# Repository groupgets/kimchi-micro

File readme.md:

# kimχ micro

kimχ micro is a small and spicy open hardware embedded SBC that offers tons of
versitility for many different applications.

## Work in progress

This board is still a work in progress and is not yet considered production-
ready. If you wish to build this hardware yourself, expect that there may still
be some bugs.

## Features

### Application Processor

This project was undertaken with video encoding/decoding and wireless
connectivity in mind, so the i.MX8M Mini variant supports 1080p60 hardware video
encode/decode.

### Mini PCIe

The board can host a half- or full-mini PCIe module as often used for high-power
wifi chipsets. Mini PCIe is also perfect for other types of wireless such as LTE
and LoRa radios.

### USB-C

The board has a full-featured USB-C port with power source and sink
capabilities, as well as support for battery charging and power.

### Expansion

To enable different applications, kimχ micro has high-density expansion
connectors and a standard add-on module specification, as well as a Qwiic
connector for rapid prototyping or simple sensor integration.

## FAQ

### How do I pronounce kimχ

Like the spicy fermented cabbage (kimchi)

### Why did you call it that

So that when we make more of these boards, we can name them things like
saurkraut, sarmale, or cole slaw, and have a series of them called the cabbage
patch. But we really do love kimchi, and it has part of KiCad in it, and i.MX.

## License

The source files for this project are licensed under CERN-OHL-S V.2. This means
you are free to reuse all or part of this design in your own projects, provided
these projects also carry the same license.

Important Note
============
GroupGets does not provide coding, firmware, or software support of any kind and will not respond to related requests. All software and firmware provided by GroupGets are offered solely as examples or potential starting points. These repositories may be outdated and are not guaranteed to function as intended.

We do not accept returns or offer replacements due to issues related to software, firmware, or code compatibility.

The software is provided "AS IS", without warranty of any kind, express or implied, including but not limited to the warranties of merchantability, fitness for a particular purpose and non-infringement. In no event shall the authors or copyright holders be liable for any claim, damages, or other liability, whether in an action of contract, tort, or otherwise, arising from, out of, or in connection with the software or the use or other dealings in the software.

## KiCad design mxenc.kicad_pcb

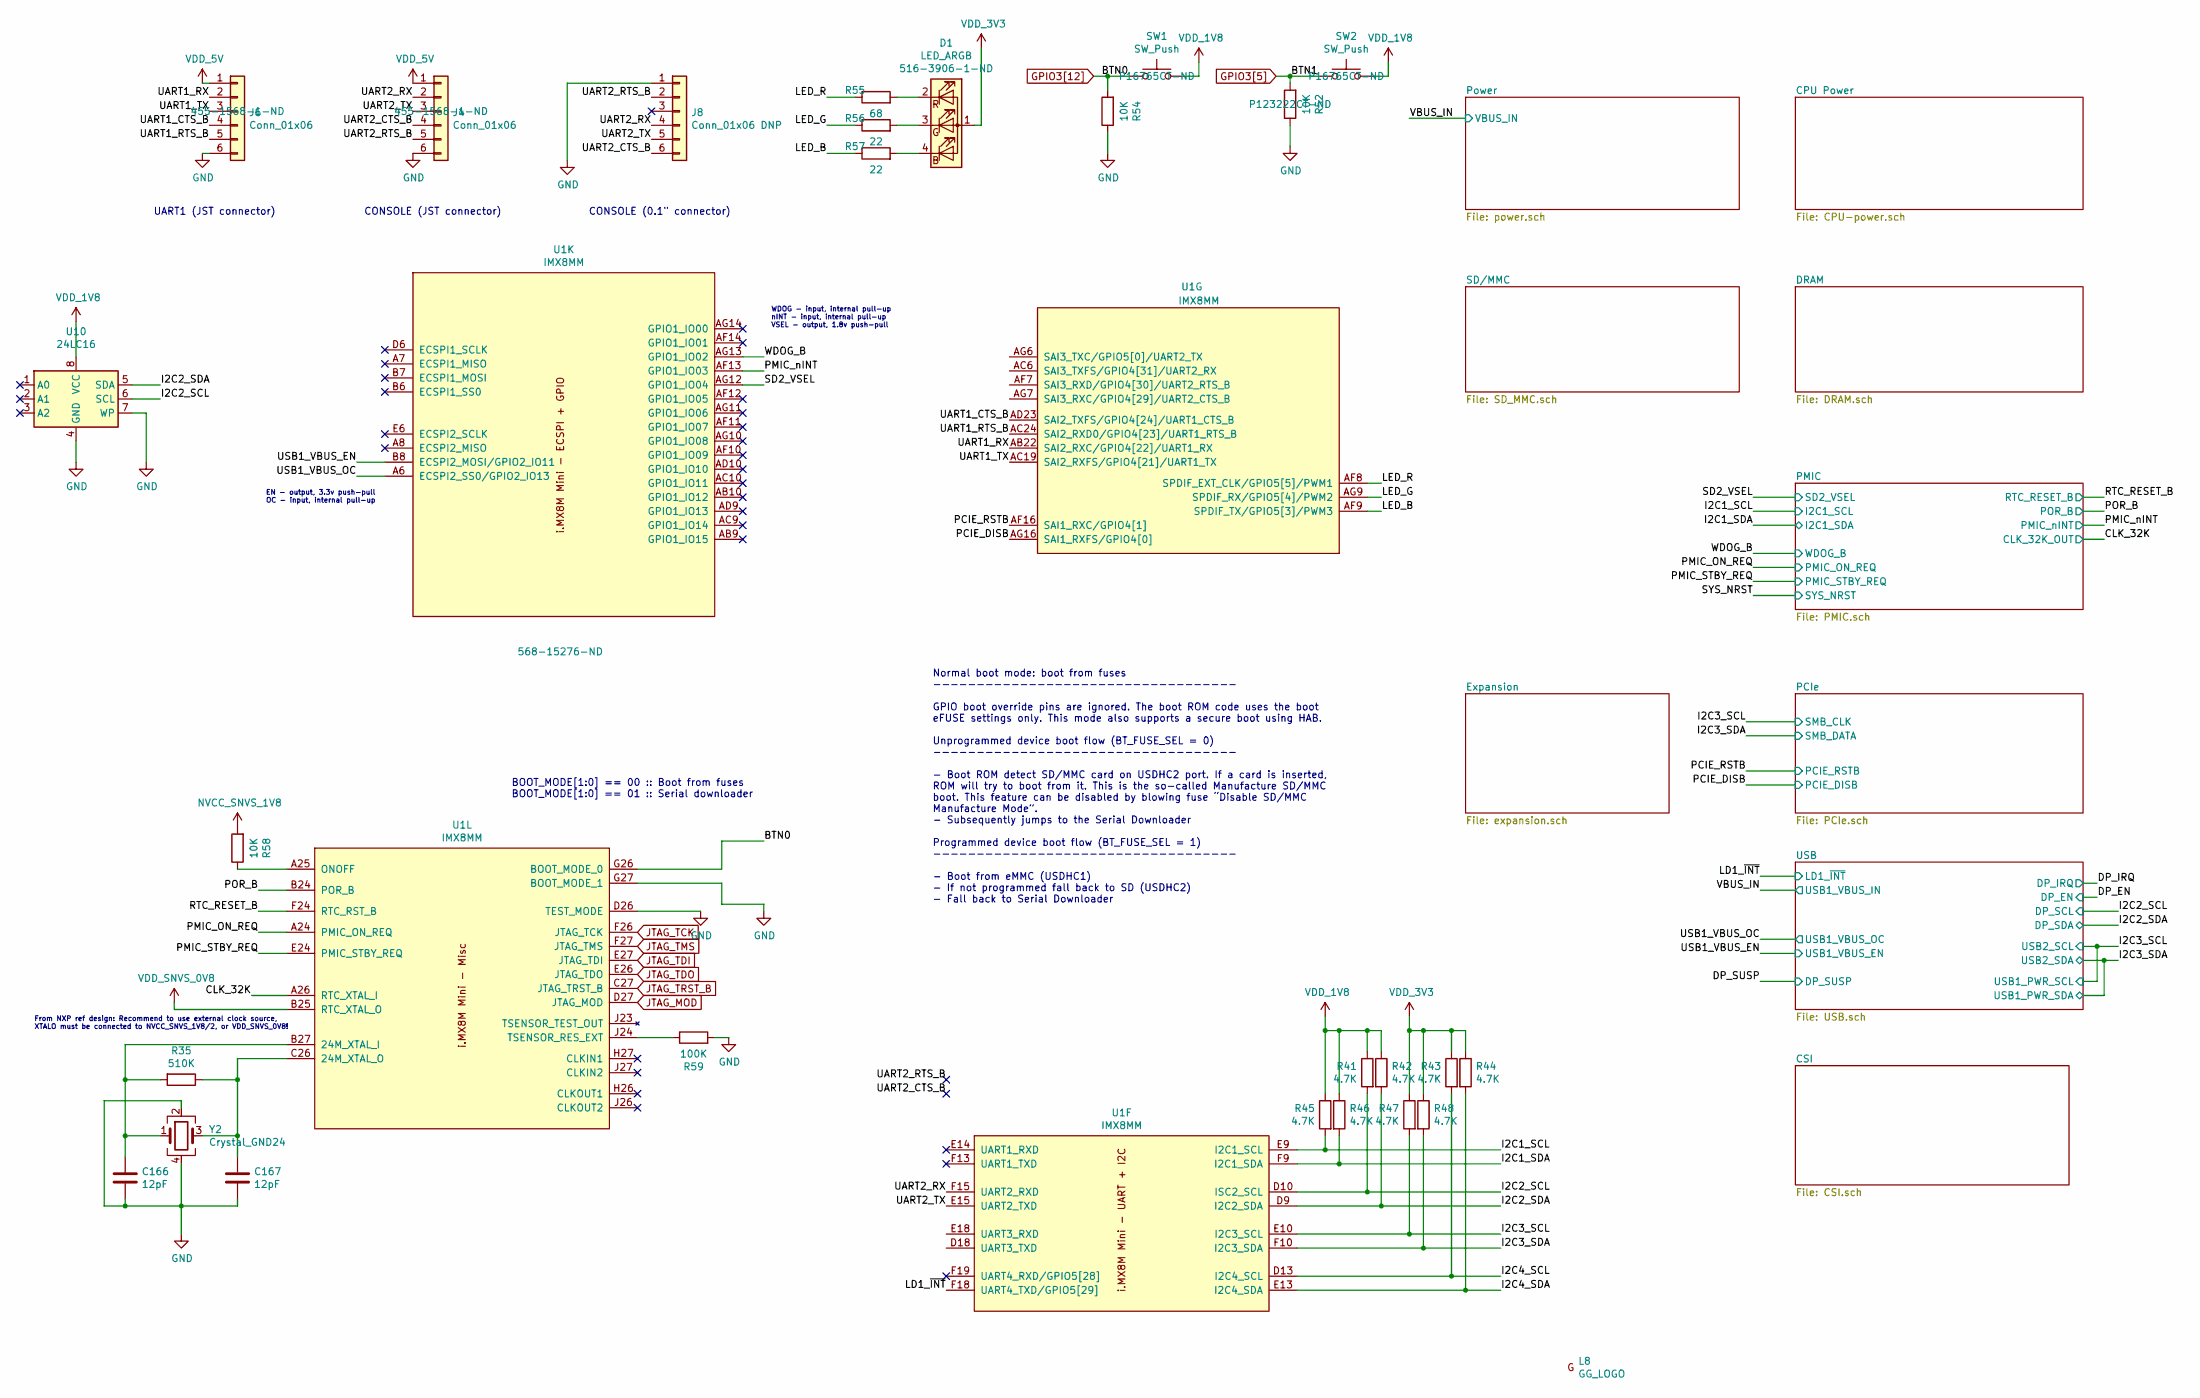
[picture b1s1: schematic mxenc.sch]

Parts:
C166, C167: 12pF; C_0201_0603Metric; Part CGA1A2C0G1E120J030BA
D1: LED_ARGB; LED_Cree-PLCC4_2x2mm_CW; Part ASMB-KTF0-0A306
J4, J6: Conn_01x06; JST_GH_SM06B-GHS-TB_1x06-1MP_P1.25mm_Horizontal; Part SM06B-GHS-TB(LF)(SN)
J8: Conn_01x06 DNP; PinHeader_1x06_P2.54mm_Horizontal
L8: GG_LOGO; gg-4x4
R35: 510K; R_0201_0603Metric; Part RC0201FR-07510KL
R41, R42, R43, R44, R45, R46, R47, R48: 4.7K; R_0201_0603Metric; Part RC0201JR-074K7L
R52, R54, R58: 10K; R_0201_0603Metric; Part ERJ-1GNJ103C
R55: 68; R_0201_0603Metric; Part RC0201JR-0768RL
R56, R57: 22; R_0201_0603Metric; Part RC0201JR-0722RL
R59: 100K; R_0201_0603Metric; Part RC0201JR-07100KL
SW1, SW2: SW_Push; SW_SPST_EVQP7C; Part EVQ-P7C01P
U1: IMX8MM; BGA-729_27x27_14.0x14.0mm; Part MIMX8MM6CVTKZAA
U10: 24LC16; DFN-8-1EP_3x2mm_P0.5mm_EP1.36x1.46mm; Part 24LC16B-I/MC
Y2: Crystal_GND24; XRCGB; Part XRCGB24M000F0L00R0

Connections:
/CLK_32K: U1.A26 (RTC_XTAL_I); also elsewhere on the board
/I2C1_SCL: R45.2, U1.E9 (I2C1_SCL); also elsewhere on the board
/I2C1_SDA: R46.2, U1.F9 (I2C1_SDA); also elsewhere on the board
/I2C2_SCL: R41.2, U1.D10 (ISC2_SCL), U10.6 (SCL)
/I2C2_SDA: R42.2, U1.D9 (I2C2_SDA), U10.5 (SDA)
/I2C3_SCL: R47.2, U1.E10 (I2C3_SCL); also elsewhere on the board
/I2C3_SDA: R48.2, U1.F10 (I2C3_SDA); also elsewhere on the board
/I2C4_SCL: R43.2, U1.D13 (I2C4_SCL)
/I2C4_SDA: R44.2, U1.E13 (I2C4_SDA)
/LD1_~INT: U1.F18 (UART4_TXD/GPIO5[29]); also elsewhere on the board
/LED_B: R57.1, U1.AF9 (SPDIF_TX/GPIO5[3]/PWM3)
/LED_G: R56.1, U1.AG9 (SPDIF_RX/GPIO5[4]/PWM2)
/LED_R: R55.1, U1.AF8 (SPDIF_EXT_CLK/GPIO5[5]/PWM1)
/PCIE_DISB: U1.AG16 (SAI1_RXFS/GPIO4[0]); also elsewhere on the board
/PCIE_RSTB: U1.AF16 (SAI1_RXC/GPIO4[1]); also elsewhere on the board
/PMIC_ON_REQ: U1.A24 (PMIC_ON_REQ); also elsewhere on the board
/PMIC_STBY_REQ: U1.E24 (PMIC_STBY_REQ); also elsewhere on the board
/PMIC_nINT: U1.AF13 (GPIO1_IO03); also elsewhere on the board
/POR_B: U1.B24 (POR_B); also elsewhere on the board
/RTC_RESET_B: U1.F24 (RTC_RST_B); also elsewhere on the board
/SD2_VSEL: U1.AG12 (GPIO1_IO04); also elsewhere on the board
/UART1_CTS_B: J6.4, U1.AD23 (SAI2_TXFS/GPIO4[24]/UART1_CTS_B)
/UART1_RTS_B: J6.5, U1.AC24 (SAI2_RXD0/GPIO4[23]/UART1_RTS_B)
/UART1_RX: J6.2, U1.AB22 (SAI2_RXC/GPIO4[22]/UART1_RX)
/UART1_TX: J6.3, U1.AC19 (SAI2_RXFS/GPIO4[21]/UART1_TX)
/UART2_CTS_B: J4.4, J8.6
/UART2_RTS_B: J4.5, J8.2
/UART2_RX: J4.2, J8.4, U1.F15 (UART2_RXD)
/UART2_TX: J4.3, J8.5, U1.E15 (UART2_TXD)
/WDOG_B: U1.AG13 (GPIO1_IO02); also elsewhere on the board
GND: C166.2, C167.2, J4.6, J6.6, J8.1, R52.1, R54.1, R59.2, U1.D26 (TEST_MODE), U1.G27 (BOOT_MODE_1), U10.4 (GND), U10.7 (WP), Y2.2, Y2.4; also elsewhere on the board
GPIO3[5]: R52.2, SW2.1; also elsewhere on the board
GPIO3[12]: R54.2, SW1.1, U1.G26 (BOOT_MODE_0); also elsewhere on the board
JTAG_MOD: U1.D27 (JTAG_MOD); also elsewhere on the board
JTAG_TCK: U1.F26 (JTAG_TCK); also elsewhere on the board
JTAG_TDI: U1.E27 (JTAG_TDI); also elsewhere on the board
JTAG_TDO: U1.E26 (JTAG_TDO); also elsewhere on the board
JTAG_TMS: U1.F27 (JTAG_TMS); also elsewhere on the board
JTAG_TRST_B: U1.C27 (JTAG_TRST_B); also elsewhere on the board
NVCC_1V8: R41.1, R42.1, R45.1, R46.1, SW1.2, SW2.2, U10.8 (VCC); also elsewhere on the board
NVCC_3V3: D1.1 (A), R43.1, R44.1, R47.1, R48.1; also elsewhere on the board
NVCC_SNVS_1V8: R58.2; also elsewhere on the board
unnamed: C166.1, R35.2, U1.B27 (24M_XTAL_I), Y2.1
unnamed: C167.1, R35.1, U1.C26 (24M_XTAL_O), Y2.3
unnamed: D1.2 (RK), R55.2
unnamed: D1.3 (GK), R56.2
unnamed: D1.4 (BK), R57.2
unnamed: R58.1, U1.A25 (ONOFF)
unnamed: R59.1, U1.J24 (TSENSOR_RES_EXT)
VDD_5V: J4.1, J6.1; also elsewhere on the board
VDD_SNVS_0V8: U1.B25 (RTC_XTAL_O); also elsewhere on the board

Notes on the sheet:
CONSOLE (JST connector)
UART1 (JST connector)
CONSOLE (0.1" connector)
From NXP ref design: Recommend to use external clock source, XTALO must be connected to NVCC_SNVS_1V8/2, or VDD_SNVS_0V8!
BOOT_MODE[1:0] == 00 :: Boot from fuses BOOT_MODE[1:0] == 01 :: Serial downloader
Normal boot mode: boot from fuses ----------------------------------- GPIO boot override pins are ignored. The boot ROM code uses the boot eFUSE settings only. This mode also supports a secure boot using HAB. Unprogrammed device boot flow (BT_FUSE_SEL = 0) ----------------------------------- - Boot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
EN - output, 3.3v push-pull OC - input, internal pull-up
WDOG - input, internal pull-up nINT - input, internal pull-up VSEL - output, 1.8v push-pull

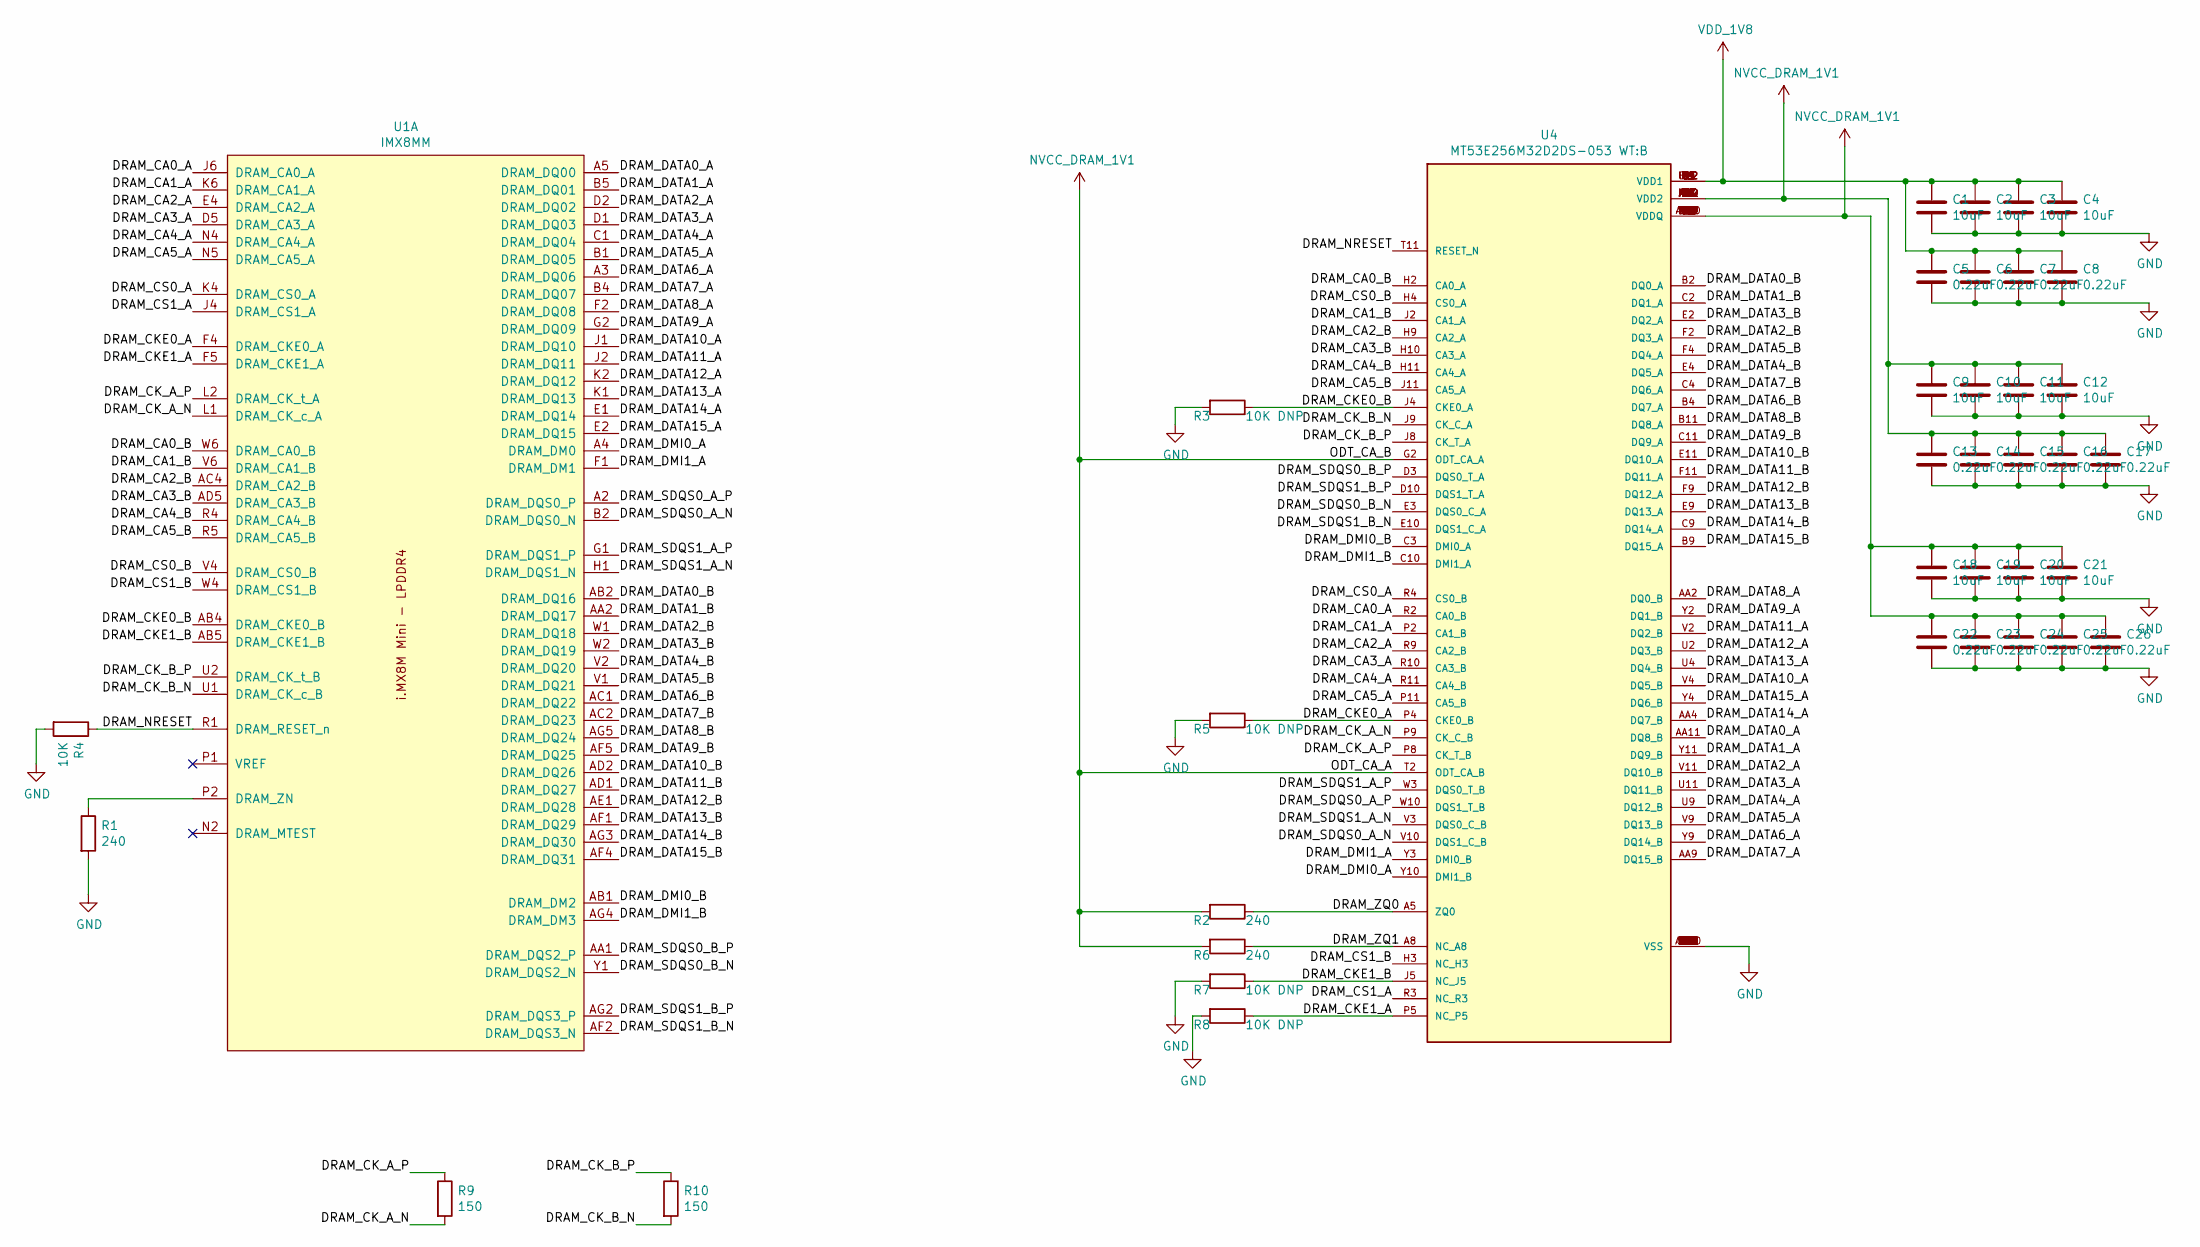
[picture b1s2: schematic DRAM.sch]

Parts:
C1, C2, C3, C4, C9, C10, C11, C12, C18, C19, C20, C21: 10uF; C_0402_1005Metric; Part GRM155C80J106ME11D
C5, C6, C7, C8, C13, C14, C15, C16, C17, C22, C23, C24, C25, C26: 0.22uF; C_0402_1005Metric; Part GRM155C8YA224ME01D
R1, R2, R6: 240; R_0402_1005Metric; Part RC0402FR-07240RP
R3, R5, R7, R8: 10K DNP; R_0402_1005Metric
R4: 10K; R_0402_1005Metric; Part ERJ-2GEJ103X
R9, R10: 150; R_0402_1005Metric; Part RC0402FR-07150RL
U1: IMX8MM; BGA-729_27x27_14.0x14.0mm; Part MIMX8MM6CVTKZAA
U4: MT53E256M32D2DS-053 WT:B; BGA200C80X65P12X22_1100X1450X80N; Part MT53E256M32D2DS-053 WT:B

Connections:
/DRAM/DRAM_CA0_A: U1.J6 (DRAM_CA0_A), U4.R2 (CA0_B)
/DRAM/DRAM_CA0_B: U1.W6 (DRAM_CA0_B), U4.H2 (CA0_A)
/DRAM/DRAM_CA1_A: U1.K6 (DRAM_CA1_A), U4.P2 (CA1_B)
/DRAM/DRAM_CA1_B: U1.V6 (DRAM_CA1_B), U4.J2 (CA1_A)
/DRAM/DRAM_CA2_A: U1.E4 (DRAM_CA2_A), U4.R9 (CA2_B)
/DRAM/DRAM_CA2_B: U1.AC4 (DRAM_CA2_B), U4.H9 (CA2_A)
/DRAM/DRAM_CA3_A: U1.D5 (DRAM_CA3_A), U4.R10 (CA3_B)
/DRAM/DRAM_CA3_B: U1.AD5 (DRAM_CA3_B), U4.H10 (CA3_A)
/DRAM/DRAM_CA4_A: U1.N4 (DRAM_CA4_A), U4.R11 (CA4_B)
/DRAM/DRAM_CA4_B: U1.R4 (DRAM_CA4_B), U4.H11 (CA4_A)
/DRAM/DRAM_CA5_A: U1.N5 (DRAM_CA5_A), U4.P11 (CA5_B)
/DRAM/DRAM_CA5_B: U1.R5 (DRAM_CA5_B), U4.J11 (CA5_A)
/DRAM/DRAM_CKE0_A: R5.1, U1.F4 (DRAM_CKE0_A), U4.P4 (CKE0_B)
/DRAM/DRAM_CKE0_B: R3.1, U1.AB4 (DRAM_CKE0_B), U4.J4 (CKE0_A)
/DRAM/DRAM_CKE1_A: R8.1, U1.F5 (DRAM_CKE1_A), U4.P5 (NC_P5)
/DRAM/DRAM_CKE1_B: R7.1, U1.AB5 (DRAM_CKE1_B), U4.J5 (NC_J5)
/DRAM/DRAM_CK_A_N: R9.2, U1.L1 (DRAM_CK_c_A), U4.P9 (CK_C_B)
/DRAM/DRAM_CK_A_P: R9.1, U1.L2 (DRAM_CK_t_A), U4.P8 (CK_T_B)
/DRAM/DRAM_CK_B_N: R10.2, U1.U1 (DRAM_CK_c_B), U4.J9 (CK_C_A)
/DRAM/DRAM_CK_B_P: R10.1, U1.U2 (DRAM_CK_t_B), U4.J8 (CK_T_A)
/DRAM/DRAM_CS0_A: U1.K4 (DRAM_CS0_A), U4.R4 (CS0_B)
/DRAM/DRAM_CS0_B: U1.V4 (DRAM_CS0_B), U4.H4 (CS0_A)
/DRAM/DRAM_CS1_A: U1.J4 (DRAM_CS1_A), U4.R3 (NC_R3)
/DRAM/DRAM_CS1_B: U1.W4 (DRAM_CS1_B), U4.H3 (NC_H3)
/DRAM/DRAM_DATA0_A: U1.A5 (DRAM_DQ00), U4.AA11 (DQ8_B)
/DRAM/DRAM_DATA0_B: U1.AB2 (DRAM_DQ16), U4.B2 (DQ0_A)
/DRAM/DRAM_DATA1_A: U1.B5 (DRAM_DQ01), U4.Y11 (DQ9_B)
/DRAM/DRAM_DATA1_B: U1.AA2 (DRAM_DQ17), U4.C2 (DQ1_A)
/DRAM/DRAM_DATA2_A: U1.D2 (DRAM_DQ02), U4.V11 (DQ10_B)
/DRAM/DRAM_DATA2_B: U1.W1 (DRAM_DQ18), U4.F2 (DQ3_A)
/DRAM/DRAM_DATA3_A: U1.D1 (DRAM_DQ03), U4.U11 (DQ11_B)
/DRAM/DRAM_DATA3_B: U1.W2 (DRAM_DQ19), U4.E2 (DQ2_A)
/DRAM/DRAM_DATA4_A: U1.C1 (DRAM_DQ04), U4.U9 (DQ12_B)
/DRAM/DRAM_DATA4_B: U1.V2 (DRAM_DQ20), U4.E4 (DQ5_A)
/DRAM/DRAM_DATA5_A: U1.B1 (DRAM_DQ05), U4.V9 (DQ13_B)
/DRAM/DRAM_DATA5_B: U1.V1 (DRAM_DQ21), U4.F4 (DQ4_A)
/DRAM/DRAM_DATA6_A: U1.A3 (DRAM_DQ06), U4.Y9 (DQ14_B)
/DRAM/DRAM_DATA6_B: U1.AC1 (DRAM_DQ22), U4.B4 (DQ7_A)
/DRAM/DRAM_DATA7_A: U1.B4 (DRAM_DQ07), U4.AA9 (DQ15_B)
/DRAM/DRAM_DATA7_B: U1.AC2 (DRAM_DQ23), U4.C4 (DQ6_A)
/DRAM/DRAM_DATA8_A: U1.F2 (DRAM_DQ08), U4.AA2 (DQ0_B)
/DRAM/DRAM_DATA8_B: U1.AG5 (DRAM_DQ24), U4.B11 (DQ8_A)
/DRAM/DRAM_DATA9_A: U1.G2 (DRAM_DQ09), U4.Y2 (DQ1_B)
/DRAM/DRAM_DATA9_B: U1.AF5 (DRAM_DQ25), U4.C11 (DQ9_A)
/DRAM/DRAM_DATA10_A: U1.J1 (DRAM_DQ10), U4.V4 (DQ5_B)
/DRAM/DRAM_DATA10_B: U1.AD2 (DRAM_DQ26), U4.E11 (DQ10_A)
/DRAM/DRAM_DATA11_A: U1.J2 (DRAM_DQ11), U4.V2 (DQ2_B)
/DRAM/DRAM_DATA11_B: U1.AD1 (DRAM_DQ27), U4.F11 (DQ11_A)
/DRAM/DRAM_DATA12_A: U1.K2 (DRAM_DQ12), U4.U2 (DQ3_B)
/DRAM/DRAM_DATA12_B: U1.AE1 (DRAM_DQ28), U4.F9 (DQ12_A)
/DRAM/DRAM_DATA13_A: U1.K1 (DRAM_DQ13), U4.U4 (DQ4_B)
/DRAM/DRAM_DATA13_B: U1.AF1 (DRAM_DQ29), U4.E9 (DQ13_A)
/DRAM/DRAM_DATA14_A: U1.E1 (DRAM_DQ14), U4.AA4 (DQ7_B)
/DRAM/DRAM_DATA14_B: U1.AG3 (DRAM_DQ30), U4.C9 (DQ14_A)
/DRAM/DRAM_DATA15_A: U1.E2 (DRAM_DQ15), U4.Y4 (DQ6_B)
/DRAM/DRAM_DATA15_B: U1.AF4 (DRAM_DQ31), U4.B9 (DQ15_A)
/DRAM/DRAM_DMI0_A: U1.A4 (DRAM_DM0), U4.Y10 (DMI1_B)
/DRAM/DRAM_DMI0_B: U1.AB1 (DRAM_DM2), U4.C3 (DMI0_A)
/DRAM/DRAM_DMI1_A: U1.F1 (DRAM_DM1), U4.Y3 (DMI0_B)
/DRAM/DRAM_DMI1_B: U1.AG4 (DRAM_DM3), U4.C10 (DMI1_A)
/DRAM/DRAM_NRESET: R4.1, U1.R1 (DRAM_RESET_n), U4.T11 (RESET_N)
/DRAM/DRAM_SDQS0_A_N: U1.B2 (DRAM_DQS0_N), U4.V10 (DQS1_C_B)
/DRAM/DRAM_SDQS0_A_P: U1.A2 (DRAM_DQS0_P), U4.W10 (DQS1_T_B)
/DRAM/DRAM_SDQS0_B_N: U1.Y1 (DRAM_DQS2_N), U4.E3 (DQS0_C_A)
/DRAM/DRAM_SDQS0_B_P: U1.AA1 (DRAM_DQS2_P), U4.D3 (DQS0_T_A)
/DRAM/DRAM_SDQS1_A_N: U1.H1 (DRAM_DQS1_N), U4.V3 (DQS0_C_B)
/DRAM/DRAM_SDQS1_A_P: U1.G1 (DRAM_DQS1_P), U4.W3 (DQS0_T_B)
/DRAM/DRAM_SDQS1_B_N: U1.AF2 (DRAM_DQS3_N), U4.E10 (DQS1_C_A)
/DRAM/DRAM_SDQS1_B_P: U1.AG2 (DRAM_DQS3_P), U4.D10 (DQS1_T_A)
/DRAM/DRAM_ZQ0: R2.1, U4.A5 (ZQ0)
/DRAM/DRAM_ZQ1: R6.1, U4.A8 (NC_A8)
GND: C1.2, C2.2, C3.2, C4.2, C5.2, C6.2, C7.2, C8.2, C9.2, C10.2, C11.2, C12.2, C13.2, C14.2, C15.2, C16.2, C17.2, C18.2, C19.2, C20.2, C21.2, C22.2, C23.2, C24.2, C25.2, C26.2, R1.2, R3.2, R4.2, R5.2, R7.2, R8.2, U4.A3 (VSS), U4.A10 (VSS), U4.AB3 (VSS), U4.AB5 (VSS), U4.AB8 (VSS), U4.AB10 (VSS), U4.C1 (VSS), U4.C5 (VSS), U4.C8 (VSS), U4.C12 (VSS), U4.D2 (VSS), U4.D4 (VSS), U4.D9 (VSS), U4.D11 (VSS), U4.E1 (VSS), U4.E5 (VSS), U4.E8 (VSS), U4.E12 (VSS), U4.G1 (VSS), U4.G3 (VSS), U4.G5 (VSS), U4.G8 (VSS), U4.G10 (VSS), U4.G12 (VSS), U4.J1 (VSS), U4.J3 (VSS), U4.J10 (VSS), U4.J12 (VSS), U4.K2 (VSS), U4.K4 (VSS), U4.K9 (VSS), U4.K11 (VSS), U4.N2 (VSS), U4.N4 (VSS), U4.N9 (VSS), U4.N11 (VSS), U4.P1 (VSS), U4.P3 (VSS), U4.P10 (VSS), U4.P12 (VSS), U4.T1 (VSS), U4.T3 (VSS), U4.T5 (VSS), U4.T8 (VSS), U4.T10 (VSS), U4.T12 (VSS), U4.V1 (VSS), U4.V5 (VSS), U4.V8 (VSS), U4.V12 (VSS), U4.W2 (VSS), U4.W4 (VSS), U4.W9 (VSS), U4.W11 (VSS), U4.Y1 (VSS), U4.Y5 (VSS), U4.Y8 (VSS), U4.Y12 (VSS); also elsewhere on the board
NVCC_1V8: C1.1, C2.1, C3.1, C4.1, C5.1, C6.1, C7.1, C8.1, U4.F1 (VDD1), U4.F12 (VDD1), U4.G4 (VDD1), U4.G9 (VDD1), U4.T4 (VDD1), U4.T9 (VDD1), U4.U1 (VDD1), U4.U12 (VDD1); also elsewhere on the board
NVCC_DRAM_1V1: C9.1, C10.1, C11.1, C12.1, C13.1, C14.1, C15.1, C16.1, C17.1, C18.1, C19.1, C20.1, C21.1, C22.1, C23.1, C24.1, C25.1, C26.1, R2.2, R6.2, U4.A4 (VDD2), U4.A9 (VDD2), U4.AA3 (VDDQ), U4.AA5 (VDDQ), U4.AA8 (VDDQ), U4.AA10 (VDDQ), U4.AB4 (VDD2), U4.AB9 (VDD2), U4.B3 (VDDQ), U4.B5 (VDDQ), U4.B8 (VDDQ), U4.B10 (VDDQ), U4.D1 (VDDQ), U4.D5 (VDDQ), U4.D8 (VDDQ), U4.D12 (VDDQ), U4.F3 (VDDQ), U4.F5 (VDD2), U4.F8 (VDD2), U4.F10 (VDDQ), U4.G2 (ODT_CA_A), U4.H1 (VDD2), U4.H5 (VDD2), U4.H8 (VDD2), U4.H12 (VDD2), U4.K1 (VDD2), U4.K3 (VDD2), U4.K10 (VDD2), U4.K12 (VDD2), U4.N1 (VDD2), U4.N3 (VDD2), U4.N10 (VDD2), U4.N12 (VDD2), U4.R1 (VDD2), U4.R5 (VDD2), U4.R8 (VDD2), U4.R12 (VDD2), U4.T2 (ODT_CA_B), U4.U3 (VDDQ), U4.U5 (VDD2), U4.U8 (VDD2), U4.U10 (VDDQ), U4.W1 (VDDQ), U4.W5 (VDDQ), U4.W8 (VDDQ), U4.W12 (VDDQ); also elsewhere on the board
unnamed: R1.1, U1.P2 (DRAM_ZN)

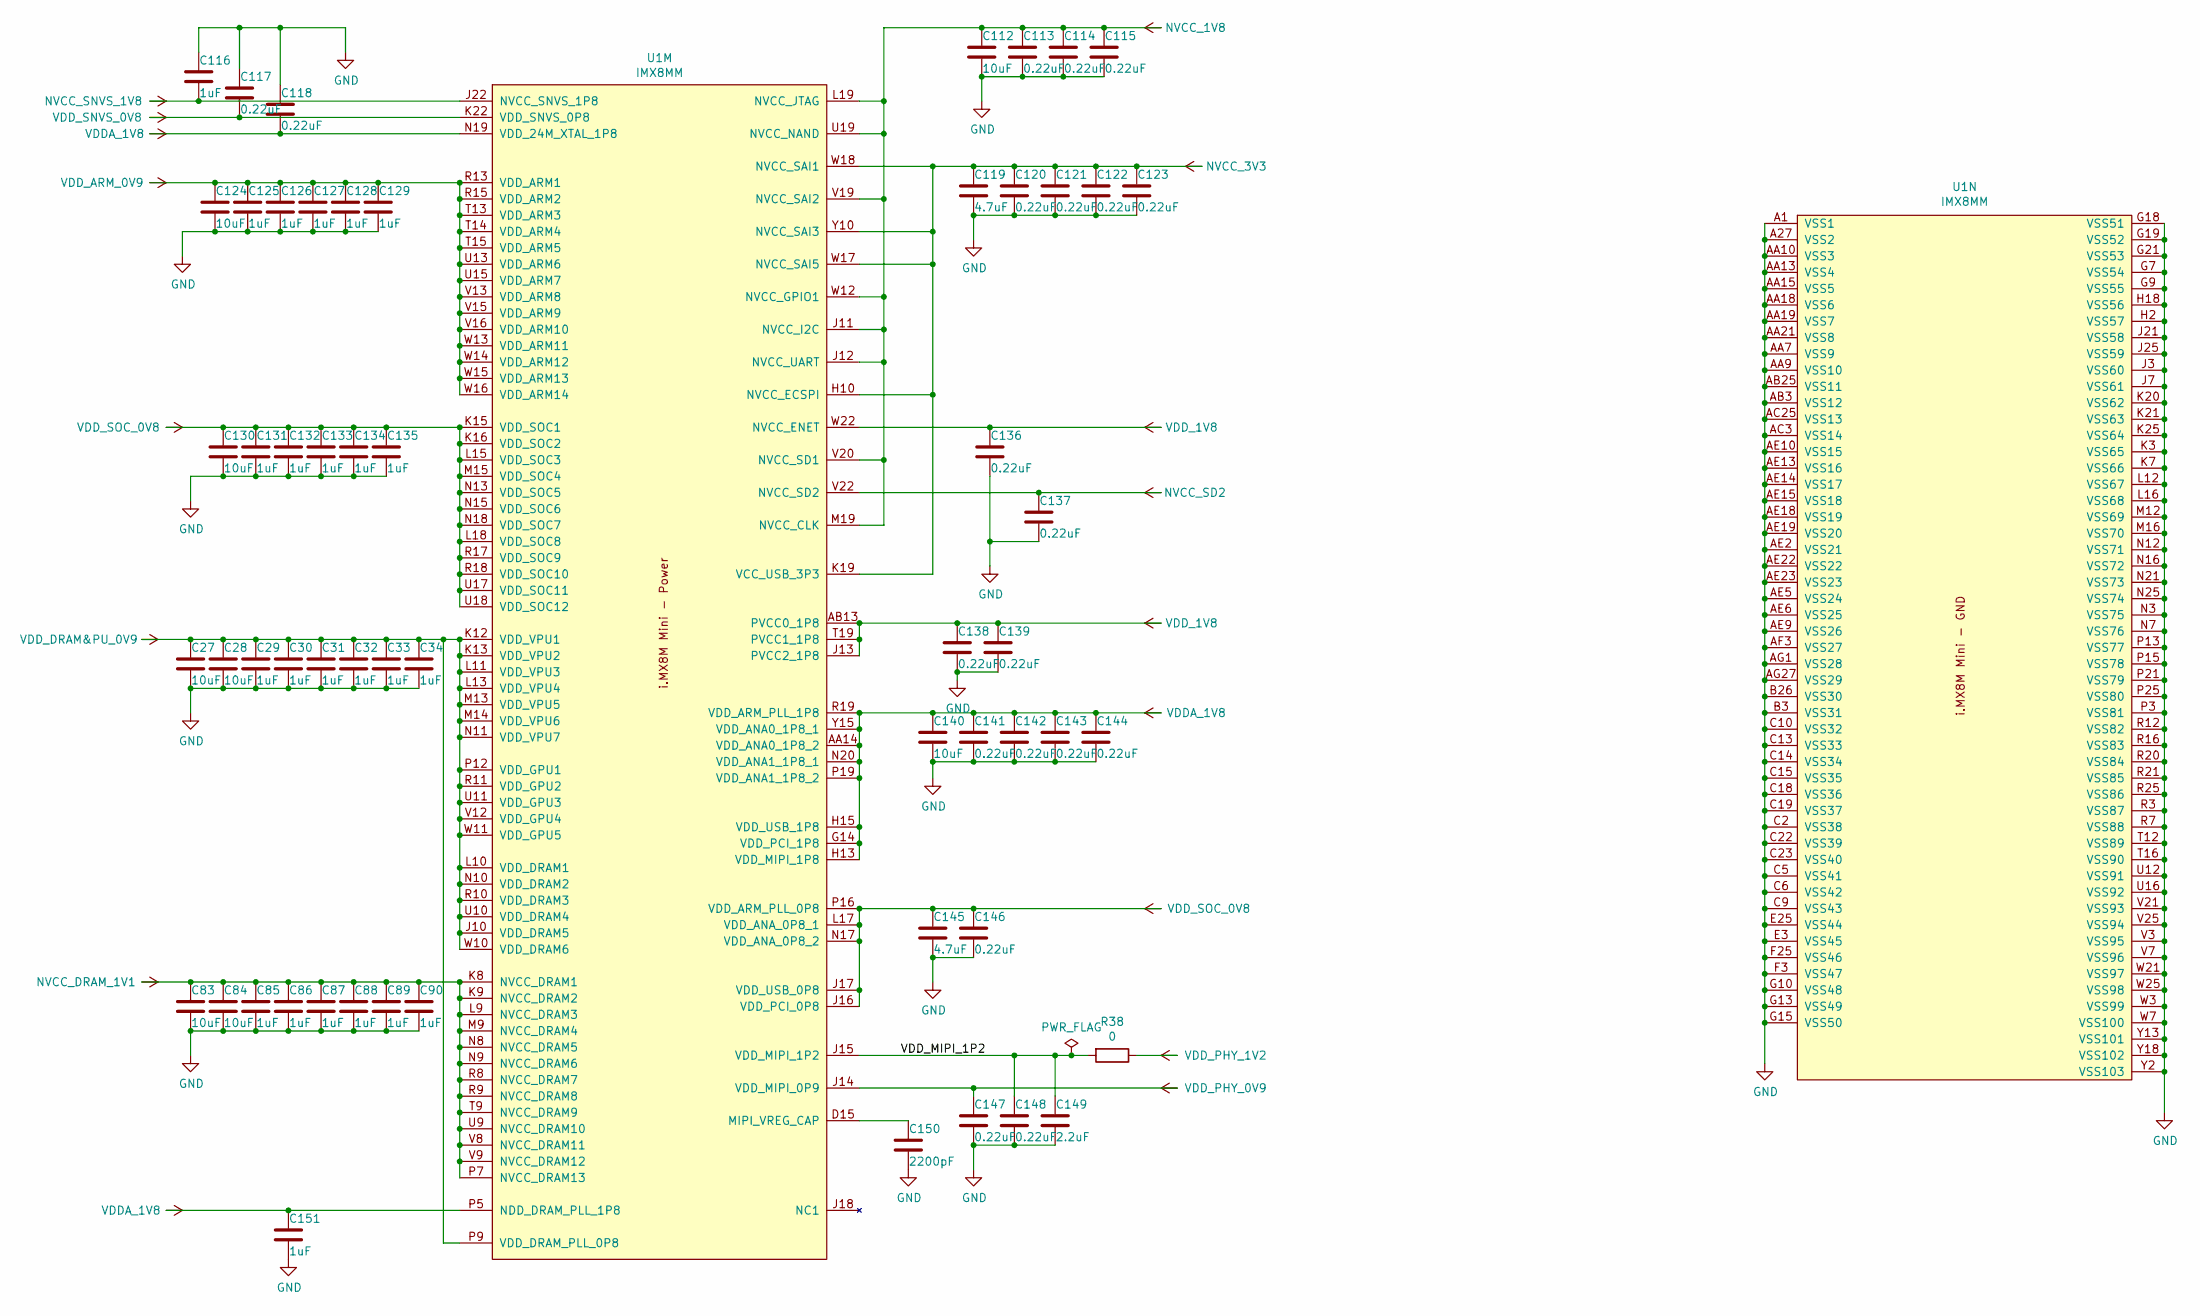
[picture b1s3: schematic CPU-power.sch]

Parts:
C27, C28, C83, C84, C112, C124, C130, C140: 10uF; C_0402_1005Metric; Part GRM155C80J106ME11D
C29, C30, C31, C32, C33, C34, C85, C86, C87, C88, C89, C90, C116, C125, C126, C127, C128, C129, C131, C132, C133, C134, C135, C151: 1uF; C_0201_0603Metric; Part GRM033C80G105ME05D
C113, C114, C115, C117, C118, C120, C121, C122, C123, C136, C137, C138, C139, C141, C142, C143, C144, C146, C147, C148: 0.22uF; C_0201_0603Metric; Part GRM033C80J224KE90D
C119, C145: 4.7uF; C_0402_1005Metric; Part GRM155C80J475MEAAD
C149: 2.2uF; C_0201_0603Metric; Part GRM033D80E225ME47D
C150: 2200pF; C_0201_0603Metric; Part GRM033R70J222KA01D
R38: 0; R_0402_1005Metric; Part RC0402JR-070RL
U1: IMX8MM; BGA-729_27x27_14.0x14.0mm; Part MIMX8MM6CVTKZAA

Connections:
/CPU Power/VDD_MIPI_1P2: C148.1, C149.1, R38.2, U1.J15 (VDD_MIPI_1P2)
GND: C27.2, C28.2, C29.2, C30.2, C31.2, C32.2, C33.2, C34.2, C83.2, C84.2, C85.2, C86.2, C87.2, C88.2, C89.2, C90.2, C112.2, C113.2, C114.2, C115.2, C116.1, C117.1, C118.1, C119.2, C120.2, C121.2, C122.2, C123.2, C124.2, C125.2, C126.2, C127.2, C128.2, C129.2, C130.2, C131.2, C132.2, C133.2, C134.2, C135.2, C136.2, C137.2, C138.2, C139.2, C140.2, C141.2, C142.2, C143.2, C144.2, C145.2, C146.2, C147.2, C148.2, C149.2, C150.2, C151.2, U1.A1 (VSS1), U1.A27 (VSS2), U1.AA7 (VSS9), U1.AA9 (VSS10), U1.AA10 (VSS3), U1.AA13 (VSS4), U1.AA15 (VSS5), U1.AA18 (VSS6), U1.AA19 (VSS7), U1.AA21 (VSS8), U1.AB3 (VSS12), U1.AB25 (VSS11), U1.AC3 (VSS14), U1.AC25 (VSS13), U1.AE2 (VSS21), U1.AE5 (VSS24), U1.AE6 (VSS25), U1.AE9 (VSS26), U1.AE10 (VSS15), U1.AE13 (VSS16), U1.AE14 (VSS17), U1.AE15 (VSS18), U1.AE18 (VSS19), U1.AE19 (VSS20), U1.AE22 (VSS22), U1.AE23 (VSS23), U1.AF3 (VSS27), U1.AG1 (VSS28), U1.AG27 (VSS29), U1.B3 (VSS31), U1.B26 (VSS30), U1.C2 (VSS38), U1.C5 (VSS41), U1.C6 (VSS42), U1.C9 (VSS43), U1.C10 (VSS32), U1.C13 (VSS33), U1.C14 (VSS34), U1.C15 (VSS35), U1.C18 (VSS36), U1.C19 (VSS37), U1.C22 (VSS39), U1.C23 (VSS40), U1.E3 (VSS45), U1.E25 (VSS44), U1.F3 (VSS47), U1.F25 (VSS46), U1.G7 (VSS54), U1.G9 (VSS55), U1.G10 (VSS48), U1.G13 (VSS49), U1.G15 (VSS50), U1.G18 (VSS51), U1.G19 (VSS52), U1.G21 (VSS53), U1.H2 (VSS57), U1.H18 (VSS56), U1.J3 (VSS60), U1.J7 (VSS61), U1.J21 (VSS58), U1.J25 (VSS59), U1.K3 (VSS65), U1.K7 (VSS66), U1.K20 (VSS62), U1.K21 (VSS63), U1.K25 (VSS64), U1.L12 (VSS67), U1.L16 (VSS68), U1.M12 (VSS69), U1.M16 (VSS70), U1.N3 (VSS75), U1.N7 (VSS76), U1.N12 (VSS71), U1.N16 (VSS72), U1.N21 (VSS73), U1.N25 (VSS74), U1.P3 (VSS81), U1.P13 (VSS77), U1.P15 (VSS78), U1.P21 (VSS79), U1.P25 (VSS80), U1.R3 (VSS87), U1.R7 (VSS88), U1.R12 (VSS82), U1.R16 (VSS83), U1.R20 (VSS84), U1.R21 (VSS85), U1.R25 (VSS86), U1.T12 (VSS89), U1.T16 (VSS90), U1.U12 (VSS91), U1.U16 (VSS92), U1.V3 (VSS95), U1.V7 (VSS96), U1.V21 (VSS93), U1.V25 (VSS94), U1.W3 (VSS99), U1.W7 (VSS100), U1.W21 (VSS97), U1.W25 (VSS98), U1.Y2 (VSS103), U1.Y13 (VSS101), U1.Y18 (VSS102); also elsewhere on the board
NVCC_1V8: C112.1, C113.1, C114.1, C115.1, C136.1, C138.1, C139.1, U1.AB13 (PVCC0_1P8), U1.J11 (NVCC_I2C), U1.J12 (NVCC_UART), U1.J13 (PVCC2_1P8), U1.L19 (NVCC_JTAG), U1.M19 (NVCC_CLK), U1.T19 (PVCC1_1P8), U1.U19 (NVCC_NAND), U1.V19 (NVCC_SAI2), U1.V20 (NVCC_SD1), U1.W12 (NVCC_GPIO1), U1.W22 (NVCC_ENET); also elsewhere on the board
NVCC_3V3: C119.1, C120.1, C121.1, C122.1, C123.1, U1.H10 (NVCC_ECSPI), U1.K19 (VCC_USB_3P3), U1.W17 (NVCC_SAI5), U1.W18 (NVCC_SAI1), U1.Y10 (NVCC_SAI3); also elsewhere on the board
NVCC_DRAM_1V1: C83.1, C84.1, C85.1, C86.1, C87.1, C88.1, C89.1, C90.1, U1.K8 (NVCC_DRAM1), U1.K9 (NVCC_DRAM2), U1.L9 (NVCC_DRAM3), U1.M9 (NVCC_DRAM4), U1.N8 (NVCC_DRAM5), U1.N9 (NVCC_DRAM6), U1.P7 (NVCC_DRAM13), U1.R8 (NVCC_DRAM7), U1.R9 (NVCC_DRAM8), U1.T9 (NVCC_DRAM9), U1.U9 (NVCC_DRAM10), U1.V8 (NVCC_DRAM11), U1.V9 (NVCC_DRAM12); also elsewhere on the board
NVCC_SD2: C137.1, U1.V22 (NVCC_SD2); also elsewhere on the board
NVCC_SNVS_1V8: C116.2, U1.J22 (NVCC_SNVS_1P8); also elsewhere on the board
unnamed: C150.1, U1.D15 (MIPI_VREG_CAP)
VDDA_1V8: C118.2, C140.1, C141.1, C142.1, C143.1, C144.1, C151.1, U1.AA14 (VDD_ANA0_1P8_2), U1.G14 (VDD_PCI_1P8), U1.H13 (VDD_MIPI_1P8), U1.H15 (VDD_USB_1P8), U1.N19 (VDD_24M_XTAL_1P8), U1.N20 (VDD_ANA1_1P8_1), U1.P5 (NDD_DRAM_PLL_1P8), U1.P19 (VDD_ANA1_1P8_2), U1.R19 (VDD_ARM_PLL_1P8), U1.Y15 (VDD_ANA0_1P8_1); also elsewhere on the board
VDD_ARM_0V9: C124.1, C125.1, C126.1, C127.1, C128.1, C129.1, U1.R13 (VDD_ARM1), U1.R15 (VDD_ARM2), U1.T13 (VDD_ARM3), U1.T14 (VDD_ARM4), U1.T15 (VDD_ARM5), U1.U13 (VDD_ARM6), U1.U15 (VDD_ARM7), U1.V13 (VDD_ARM8), U1.V15 (VDD_ARM9), U1.V16 (VDD_ARM10), U1.W13 (VDD_ARM11), U1.W14 (VDD_ARM12), U1.W15 (VDD_ARM13), U1.W16 (VDD_ARM14); also elsewhere on the board
VDD_DRAM&PU_0V9: C27.1, C28.1, C29.1, C30.1, C31.1, C32.1, C33.1, C34.1, U1.J10 (VDD_DRAM5), U1.K12 (VDD_VPU1), U1.K13 (VDD_VPU2), U1.L10 (VDD_DRAM1), U1.L11 (VDD_VPU3), U1.L13 (VDD_VPU4), U1.M13 (VDD_VPU5), U1.M14 (VDD_VPU6), U1.N10 (VDD_DRAM2), U1.N11 (VDD_VPU7), U1.P9 (VDD_DRAM_PLL_0P8), U1.P12 (VDD_GPU1), U1.R10 (VDD_DRAM3), U1.R11 (VDD_GPU2), U1.U10 (VDD_DRAM4), U1.U11 (VDD_GPU3), U1.V12 (VDD_GPU4), U1.W10 (VDD_DRAM6), U1.W11 (VDD_GPU5); also elsewhere on the board
VDD_PHY_0V9: C147.1, U1.J14 (VDD_MIPI_0P9); also elsewhere on the board
VDD_PHY_1V2: R38.1; also elsewhere on the board
VDD_SNVS_0V8: C117.2, U1.K22 (VDD_SNVS_0P8); also elsewhere on the board
VDD_SOC_0V8: C130.1, C131.1, C132.1, C133.1, C134.1, C135.1, C145.1, C146.1, U1.J16 (VDD_PCI_0P8), U1.J17 (VDD_USB_0P8), U1.K15 (VDD_SOC1), U1.K16 (VDD_SOC2), U1.L15 (VDD_SOC3), U1.L17 (VDD_ANA_0P8_1), U1.L18 (VDD_SOC8), U1.M15 (VDD_SOC4), U1.N13 (VDD_SOC5), U1.N15 (VDD_SOC6), U1.N17 (VDD_ANA_0P8_2), U1.N18 (VDD_SOC7), U1.P16 (VDD_ARM_PLL_0P8), U1.R17 (VDD_SOC9), U1.R18 (VDD_SOC10), U1.U17 (VDD_SOC11), U1.U18 (VDD_SOC12); also elsewhere on the board

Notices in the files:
hardware_sbc/CPU-power.sch:
https://www.ohwr.org/project/cernohl/wikis/Documents/CERN-OHL-version-2
Licensed CERN-OHL-S V.2
Copyright © 2020 GroupGets, LLC
